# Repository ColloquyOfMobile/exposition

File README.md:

# exposition
Colloquy of Mobiles for exposition in ZKM

## Todo
In KiCad:
- Choose the footprint for power supply capacitor.
- Check dimension of jack barrel.
- For unexpected error on the Colloquy-PC, catch them, show them to the user, invite the user to add additional information, invite the user to log (with context), commit and push.

## Todo: software roadmap

Ordered by priority: get it running reliably first, then make it easy to
retune without code changes, then make faults easy to diagnose, then
polish the day-to-day experience.

### 1. Up and running (do this before anything else)

- **Validate on real hardware.** Everything built and tested this
  refactor ran in simulation (`Base.is_simulated` is only `False` on the
  `Colloquy-Laptop` hostname) - nothing has touched a real Dynamixel or
  Arduino yet. Run `main.py` on the actual machine and confirm servo
  comms, Arduino serial comms, and LED behavior before relying on
  anything else here.
- **Pin `requirements.txt` completely.** It only lists `yattag` and
  `dynamixel_sdk`, but `pyserial` (imported as `serial` in
  `hardware/arduino/`, `hardware/com_port/`, `hardware/u2d2/`) is a hard
  runtime dependency that isn't listed - `pip install -r
  requirements.txt` alone won't actually be enough to run the app on a
  fresh machine.
- **Implement `Colloquy.close()`.** Currently `raise
  NotImplementedError` unconditionally (with dead code after it) - there
  is no clean, non-emergency shutdown path besides the `/shutdown` web
  route. Decide what it should actually do (stop threads, release
  hardware) and implement it.
- **Decide the fate of the male-blink / female-read-pattern behavior.**
  This is the installation's actual interactive concept (see CLAUDE.md:
  each male blinks an identity + requested-drive-state pattern, a female
  is meant to read it and respond) - but `Search.loop()`/`setup()`
  deliberately `raise NotImplementedError("use the turn_back_and_forth
  thread")` right now, so females just turn back and forth instead. Is
  that simplification intentional/permanent for this exhibition, or does
  `ReadPattern` need to be wired up before opening? This is an artistic
  decision as much as a technical one - flag it and decide deliberately
  rather than by default.
- **Confirm the emergency-stop path is enough for unattended operation.**
  `/emergency-stop`, `/shutdown`, `/restart` exist and work, but this is
  a museum installation that will run unattended for stretches - is a
  web route sufficient, or is a physical panic button / auto-restart-on-
  crash needed too?
- **Test USB/serial resilience.** Arduino/U2D2 connections open lazily
  on first use; there's already a "waiting for Arduino to reboot"
  pattern at startup, but reconnect-after-fault (cable unplugged and
  replugged mid-show, Arduino resets on its own) hasn't been exercised.

### 2. Flexible (retune without touching code)

- The new **params tab** (`/app/params`) is the first big step here -
  every value in `local/params.json` is now live-viewable/editable from
  the web UI. Worth a pass during real setup to confirm the values staff
  will actually want to retune on-site (light thresholds, interaction
  origins, per-body drive timing) are all comfortably reachable there.
- **Decide what (if anything) in the `#`-prefixed archive is actually
  planned-but-unfinished work**, vs. permanently retired. CLAUDE.md
  preserves it as reference rather than dead code by convention, and this
  refactor found real orphaned/broken functionality nearby it (a
  `Conversation` concept, a `Mirror` concept, both deleted this pass as
  unreachable) - worth one deliberate pass to confirm nothing there was
  actually meant to ship.
- **Audit which hardcoded constants are likely to need on-site tuning**
  (e.g. the 0.5s blink step, the light-pattern bit sequences) and move
  the ones that do into `params.json` alongside everything else now that
  there's a UI for it.

### 3. Debuggable (diagnose faults quickly when something goes wrong)

- **Fix `ThreadErrors`/`ThreadError`'s stale one-arg `snapshot(path)`
  override** - it shadows the working inherited
  `Base.snapshot(path, focus_path)`, the same crash pattern fixed
  throughout this refactor everywhere else, but explicitly left for
  later since it only matters once a thread actually errors. That's
  exactly the moment you need it to work during a live show, so worth
  fixing before relying on it.
- **Build a live status/health view.** Right now, diagnosing anything
  means clicking through the generic tree browser node by node. A single
  page showing every body's position, torque state, and light-sensor
  reading, plus any `thread_errors`, at a glance would cut diagnosis time
  a lot during setup and rehearsal.
- **Put the chart tooling built this refactor to real use**
  (`ui/graph_view.py`, `tests > test graph`, `test_sensors`) - wire up
  light-sensor and position logging during rehearsal runs so behavior can
  be reviewed afterward, not only watched live.
- **Stop wiping logs on every restart.** `colloquy/logger.py` clears
  `local/logs/` on process start - if something crashes overnight
  unattended, the log explaining why is gone before anyone looks.
  Archive the previous run's logs instead of deleting them.
- **Coverage sits around 46%** on the new unit test suite - expected and
  fine, since hardware I/O and thread-loop bodies aren't unit-testable by
  design (confirmed this refactor, not a red flag by itself). It does
  mean bugs in `loop()`/`setup()`/`setdown()` bodies can only be caught
  by actually running them, so budget a deliberate rehearsal-testing pass
  on real hardware rather than trusting the test suite's green alone.

### 4. A bit more user-friendly (once the above is solid)

- The web UI is a generic tree browser - functional, but not really
  designed for a non-developer to operate confidently during a show.
  Once the above is stable, a small purpose-built front page (start/
  stop, current status, the handful of common actions) would go a long
  way for staff who don't know the underlying tree structure.
- Two small pre-existing bugs surfaced but left out of scope this
  refactor, worth a quick fix once things are stable: `input/__init__.py`'s
  `commands` property references undefined `Key`/`Space` (crashes if ever
  exercised); `hardware/neopixels/commands/close.py` and
  `tests/test_neopixels/commands/close.py` reference an undefined
  `HTML`/`Action` from an already-commented-out import.
- Once real rehearsal data exists (see "chart tooling" above), invest in
  presenting it well - the server-drawn graph already pages and thins, so
  this is mostly a matter of pointing it at real logged data.

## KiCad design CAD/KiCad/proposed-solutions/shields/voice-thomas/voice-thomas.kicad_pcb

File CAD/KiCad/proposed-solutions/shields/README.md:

# Colloquy shield PCB set

Updated for SHIELDS.md revision d076edc (2026-10-13) and MICROPHONE_BOARD.md.
All current KiCad 9 projects and their shared library are in this folder.

Blender assembly scenes, previews and export tools are in
[CAD/Blender/pcb-assemblies](../../../Blender/pcb-assemblies/README.md).

Matching functional pinouts show signal origins and destinations around a
rectangle, with processor pins in its centre:
[Arduino Mega](<../../../../Source code/Python/colloquy/server2/static/hardware/shields-mega-pinout.svg>)
and [Teensy](<../../../../Source code/Python/colloquy/server2/static/hardware/shields-teensy-pinout.svg>).
`SHIELDS.md` section 1a shows both. Regenerate from the repository root with
`py export_shields_pinout.py`; the generator checks its mapping against the PCBs.

| Project | Function | Quantity |
|---|---|---|
| backplane | Harness, power, shield slots, eight LEDs and 26 test headers | 1 |
| teensy-adapter | Teensy 4.1 in the Mega slot; three power test headers | 1 |
| voice-thomas | Thomas RC filter for either processor; THT pitch components | 5, more as needed |
| microphone-flex | Rev C MAX9814 holder, 32 x 62 mm, left/right/up module sockets, removable selectors | 6 (one spare) |
| analyser-carrier | Five converted DFRobot modules, direct plug-in sockets | 1 |

The active filter is obsolete. One voice layout supports all five Thomas
populations and thirteen new-pitch populations. See ASSEMBLY.md and its BOMs.
The old active voice and bare-chip analyser files are clearly archived under
../../old-reference/superseded-shields/ and are not current build inputs.

Open each current .kicad_pro. Main .kicad_pcb files are routed; -placed files
are unrouted checkpoints. Backplane/adapter use four copper layers; voice/mic
two; nominal thickness is 1.6 mm. Symbols and footprints are local.
Native ERC/DRC, netlist parity and interface results are in VALIDATION.md/json.

Current order packages are in ../../production/assembly/; see ../../README.md.
The analyser carrier uses user-authorized photo-derived mounts with tolerance slots; confirm fit with its 1:1 template. The microphone
module's actual pin/hole grid and seated connector height must be confirmed. REVIEW.md
lists outstanding physical checks. The carrier retains the original 150 x 55mm backplane envelope and retention points.

Generation: scripts/design.py, boards.py, variants.py with KiCad's Python.
The analyser carrier has its own generator, scripts/carrier.py; the microphone
holder is microphone-flex/microphone-flex.kicad_pcb; its README documents the
approved placement, routing and initial selector settings. The old holder generator
is historical and must not replace the selected flex board.
Routing: scripts/route.py with Freerouting 2.4.1. After routing, run labels.py,
finish.py, planes.py, check.py and verify.py, then the repository root's
mark_polarity.py (+ and - beside every polarized part). Preserve mechanical holes and
validated connector positions when regenerating. Historical migration scripts
are one-time tools, not general rebuild commands. Router files stay in tmp/.
positions.csv contains front SMD placements for outsourced boards; fit THT parts manually from BOMs
and assembly views. Filter all populations by their selected BOM.

All SMD parts are on the front. The adapter's CM1-CM5 are beside the Teensy
socket, clear of its body. Outsource front SMD assembly for the backplane,
adapter, voice card (R3) and flex microphone holder. Current manufacturing ZIPs
include exact SMD BOMs and matching CPL files. Fit through-hole parts and modules
by hand; the analyser carrier has no SMD population.

## Microphone on the module's L input — 2026-10-19

Each DFRobot module now takes its microphone on L, so the conversion moves to
the right channel: remove R3 (the right-input 22K) and jumper the isolated R
to OUT. The carrier schematic, routed copper, silkscreen and fabrication
packages now follow SHIELDS.md 4b and analyser-carrier/README.md
(RELEASE_REVIEW.md F7, resolved). All module and retention positions are preserved.

## Front computing slot and servo supply — 2026-10-08

The 2026-10-08 backplane also puts the computing slot on the DSUB/front face,
mirrored about x=167.83 mm, with holes matching the unchanged Teensy adapter.
USB/jack rule areas exclude pads and vias. Computing-slot spacers must be
round and <=4 mm OD on the front, with screw heads on the rear (ASSEMBLY.md).
+12V is routed at >=2 mm entirely on outer copper, enforced by native DRC
rules and independent verification.

## Direct-plug carrier revision — 2026-10-07

The analyser carrier now uses female sockets beneath modified modules. No
module-to-carrier leads remain. Each module requires removal of its left-input
22K resistor R4, an on-module jumper from isolated L to OUT, and downward
male headers (since 2026-10-19: R3 and R instead, above). Read
analyser-carrier/README.md before assembly. Socket positions
are photo-derived; check all contacts against the updated 1:1 template.

## Restored enclosure mounts — 2026-10-21

The backplane now retains the four original 8 mm enclosure cutouts recovered
from `CAD/KiCad/old-reference/original-supplied-boards/electronic box/`. Their centres are measured from the
outside board envelope, preserving the original pattern exactly. TPL3 moved
locally and affected tracks were rerouted to clear the centre and left holes.
See [the dimensions and transfer notes](<backplane/ENCLOSURE_MOUNTING.md>) and
[the mounting layout](<backplane/enclosure-mounting-layout.svg>).
After regenerating a staging board, run `scripts/restore_enclosure_holes.py`
before routing; rerun DRC and export fabrication files after any layout edit.

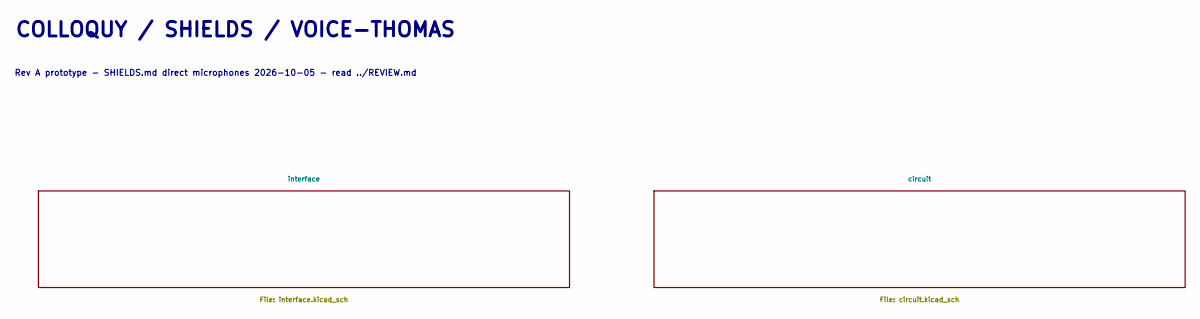
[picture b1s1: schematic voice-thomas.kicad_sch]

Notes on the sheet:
COLLOQUY / SHIELDS / VOICE-THOMAS
Rev A prototype - SHIELDS.md direct microphones 2026-10-05 - read ../REVIEW.md

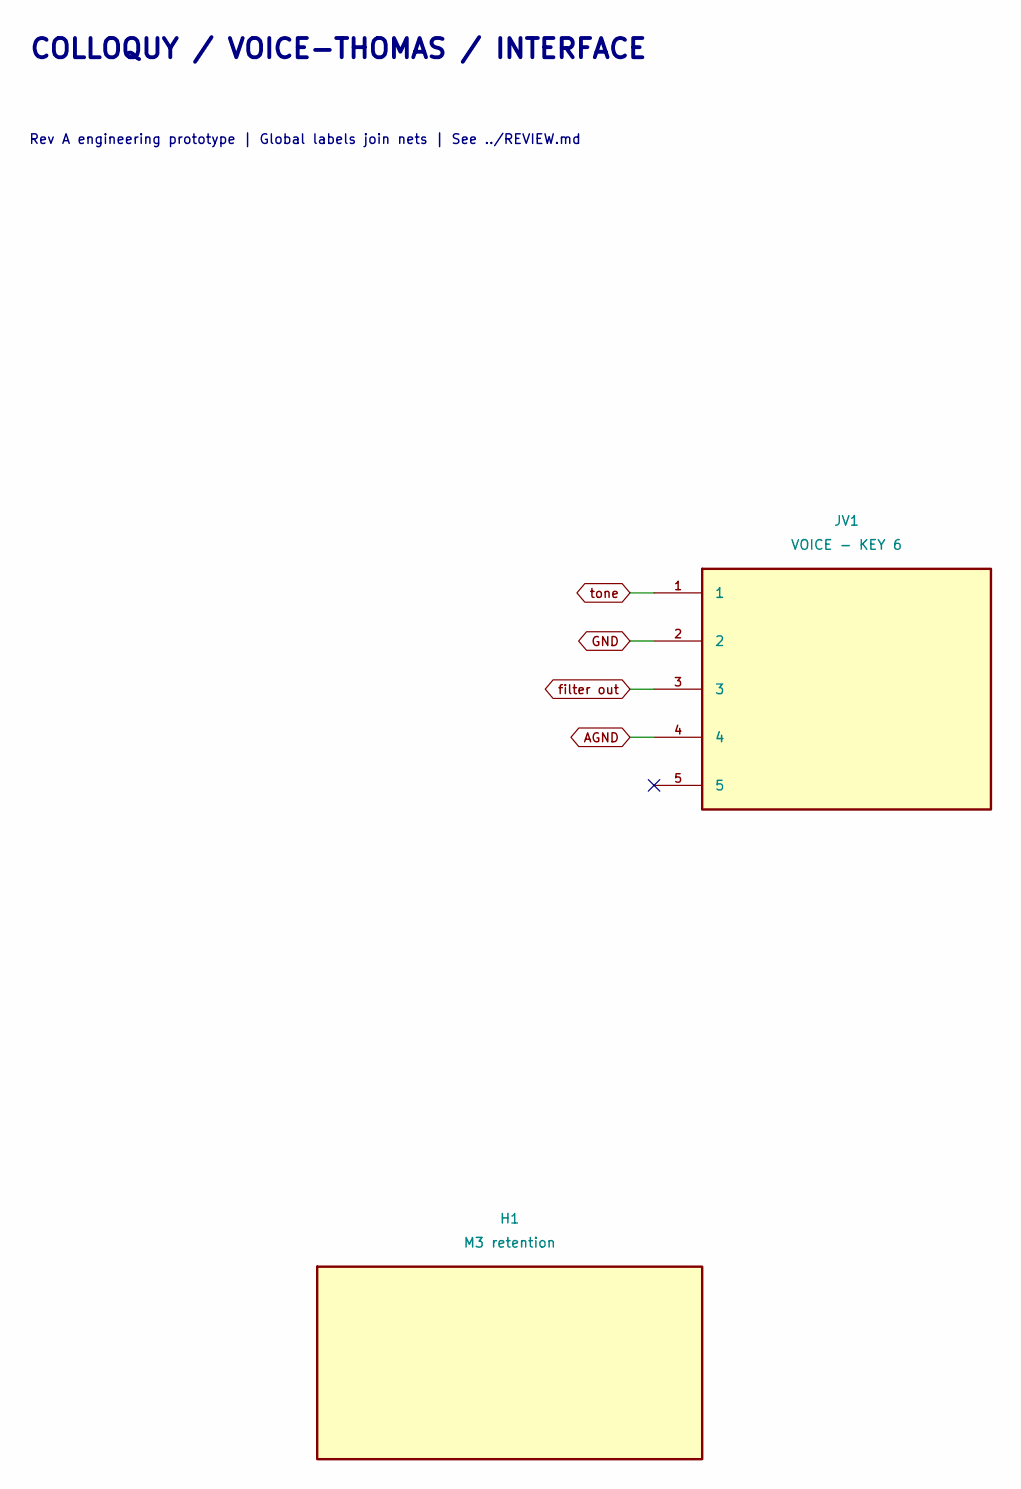
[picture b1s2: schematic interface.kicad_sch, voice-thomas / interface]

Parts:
H1: M3 retention; MountingHole_3.2mm_M3
JV1: VOICE - KEY 6; Socket_2x03_Key6

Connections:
AGND: JV1.4; also elsewhere on the board
GND: JV1.2; also elsewhere on the board
filter out: JV1.3; also elsewhere on the board
tone: JV1.1; also elsewhere on the board

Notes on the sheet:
COLLOQUY / VOICE-THOMAS / INTERFACE
Rev A engineering prototype | Global labels join nets | See ../REVIEW.md

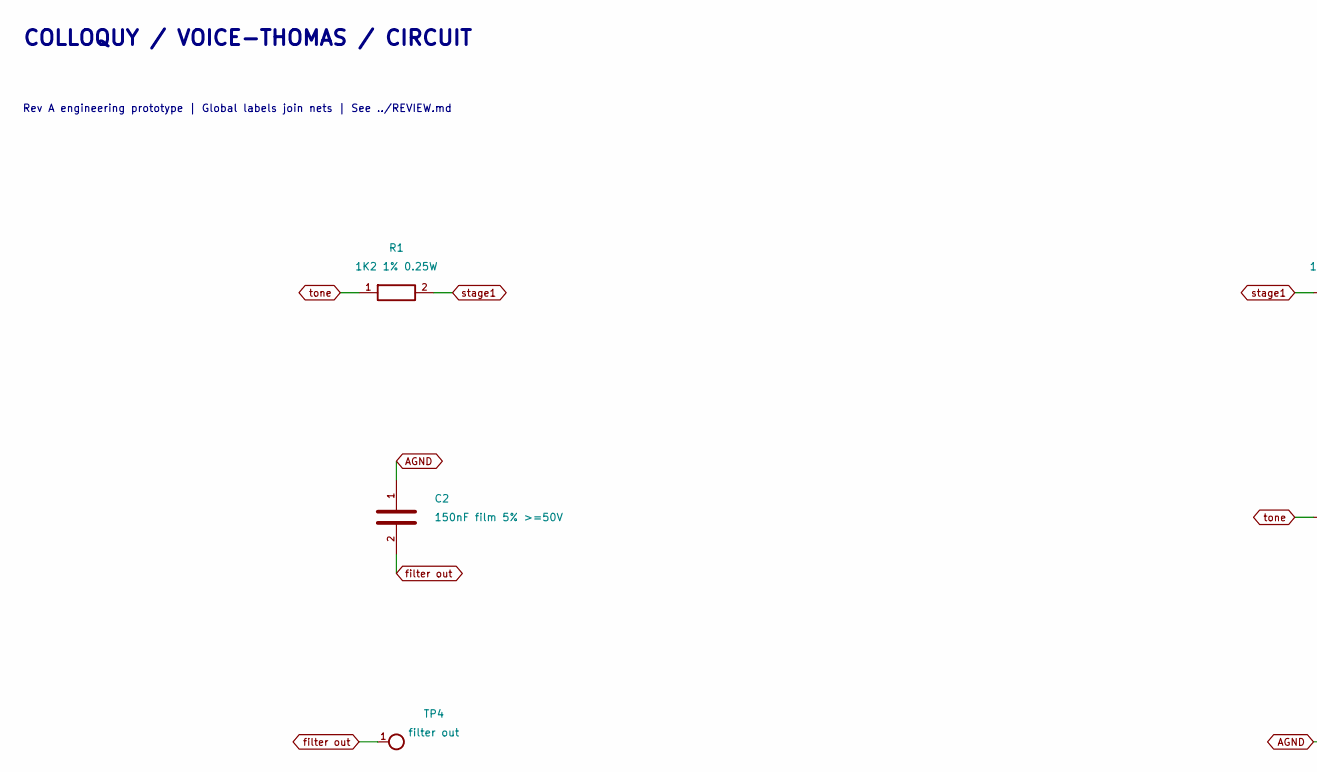
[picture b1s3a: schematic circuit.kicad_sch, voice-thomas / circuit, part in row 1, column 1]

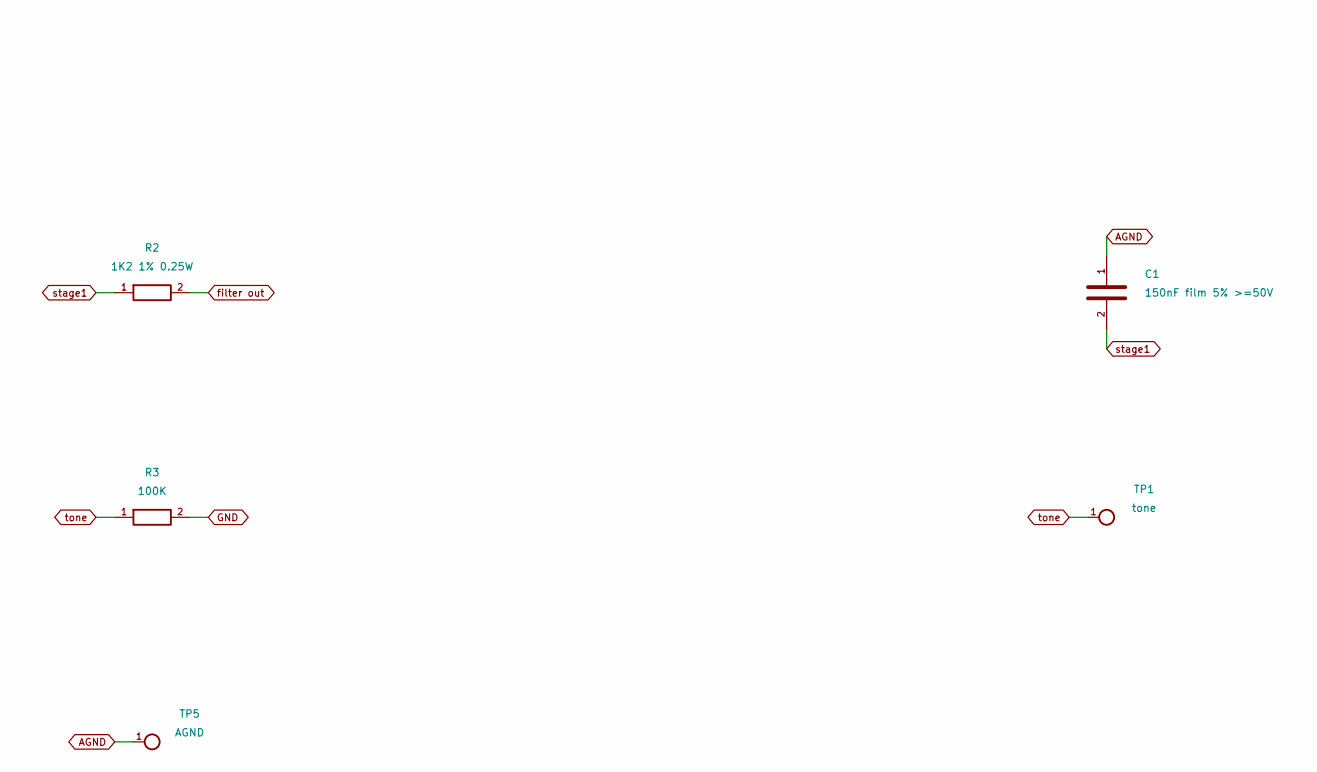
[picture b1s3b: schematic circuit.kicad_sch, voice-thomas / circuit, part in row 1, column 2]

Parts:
C1, C2: 150nF film 5% >=50V; C_Rect_L7.0mm_W6.5mm_P5.00mm
R1, R2: 1K2 1% 0.25W; R_Axial_DIN0207_L6.3mm_D2.5mm_P7.62mm_Horizontal
R3: 100K; R_Axial_DIN0207_L6.3mm_D2.5mm_P7.62mm_Horizontal
TP1: tone; TestPoint_Pad_D1.5mm
TP4: filter out; TestPin_1x01_P2.54mm
TP5: AGND; TestPin_1x01_P2.54mm

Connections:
AGND: C1.1, C2.1, TP5.1; also elsewhere on the board
GND: R3.2; also elsewhere on the board
filter out: C2.2, R2.2, TP4.1; also elsewhere on the board
stage1: C1.2, R1.2, R2.1
tone: R1.1, R3.1, TP1.1; also elsewhere on the board

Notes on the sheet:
COLLOQUY / VOICE-THOMAS / CIRCUIT
Rev A engineering prototype | Global labels join nets | See ../REVIEW.md

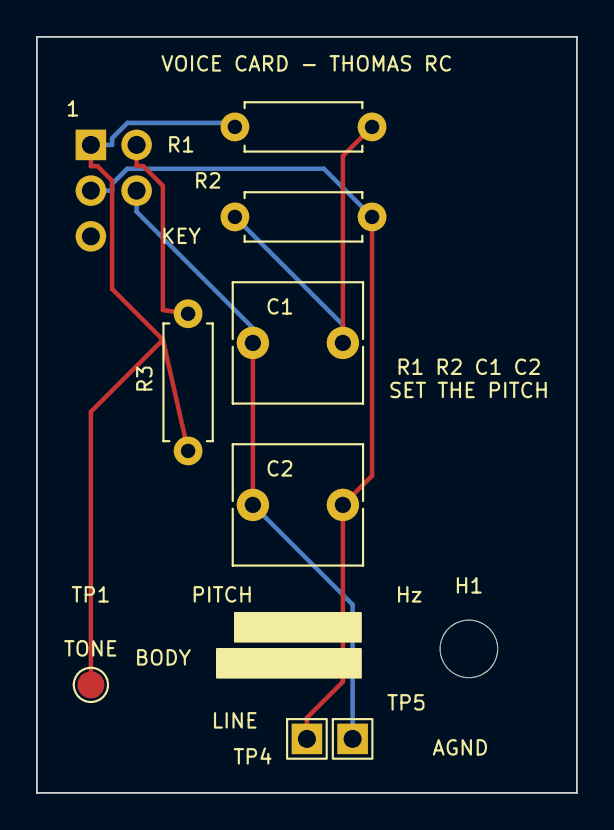
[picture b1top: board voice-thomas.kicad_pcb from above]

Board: 2 copper layers, 30.0 x 42.0 mm, 10 parts (1 on the bottom side), 5 nets.

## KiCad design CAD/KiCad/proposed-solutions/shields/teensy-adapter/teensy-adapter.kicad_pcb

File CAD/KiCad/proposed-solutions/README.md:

# Editable designs

Current replacement designs and alternatives live here. Only the seven boards listed
in [the electronics index](../README.md) are selected for manufacture. In particular,
`electronic box v2` and `thomas-or-teensy` are alternative main-board studies.

Use `shields/microphone-flex` for the production microphone holder. Original boards
are preserved under `../old-reference`; purchased-module references are under
`../provided-elements`. Generated order files are under `../production`.

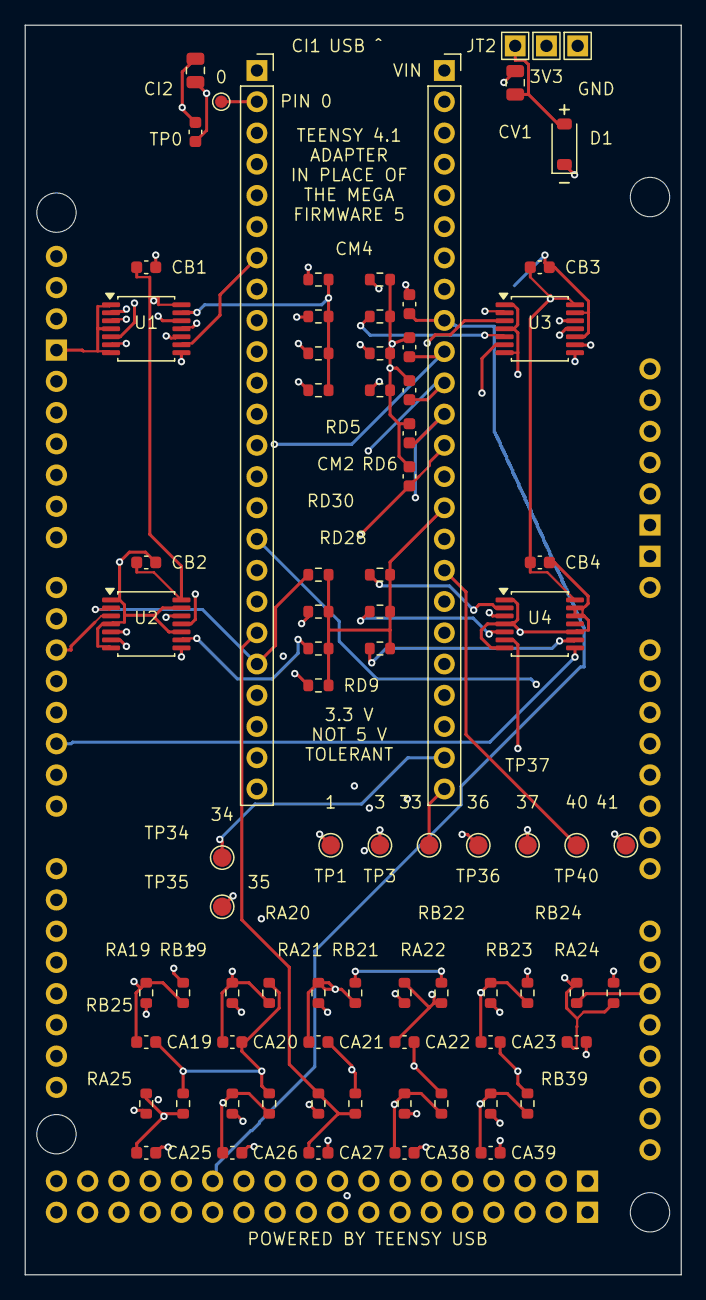
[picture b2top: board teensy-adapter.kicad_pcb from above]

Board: 4 copper layers, 53.3 x 101.6 mm, 85 parts (1 on the bottom side), 71 nets.

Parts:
CA19, CA20, CA21, CA22, CA23, CA24, CA25, CA26, CA27, CA38, CA39: 10nF C0G; C_0603_1608Metric
CB1, CB2, CB3, CB4: 100nF; C_0603_1608Metric
CI1: 10uF X7R; C_0805_2012Metric
CI2: 100nF; C_0603_1608Metric
CM1, CM2, CM3, CM4, CM5: 1nF C0G; C_0603_1608Metric
CV1: 10uF X7R; C_0805_2012Metric
D1: 1N5819HW; D_SOD-123
HM1, HM2, HM3, HM4: M3 computing shield; MountingHole_3.2mm_M3
JM1: MEGA PATTERN FEMALE; Mega_Female
JT1: Teensy 4.1 JT1; PinSocket_1x24_P2.54mm_Vertical
JT2: Teensy 4.1 JT2; PinSocket_1x24_P2.54mm_Vertical
RA19, RA20, RA21, RA22, RA23, RA24, RA25, RA26, RA27, RA38, RA39: 100K; R_0603_1608Metric
RB19, RB20, RB21, RB22, RB23, RB24, RB25, RB26, RB27, RB38, RB39: 150K; R_0603_1608Metric
RD2, RD4, RD5, RD6, RD7, RD8, RD9, RD10, RD11, RD12, RD28, RD29, RD30, RD31, RD32: 100K; R_0603_1608Metric
TP0: gpio/0; TestPoint_Pad_D1.0mm
TP1: gpio/1; TestPoint_Pad_D1.5mm
TP3: gpio/3; TestPoint_Pad_D1.5mm
TP33: gpio/33; TestPoint_Pad_D1.5mm
TP34: gpio/34; TestPoint_Pad_D1.5mm
TP35: gpio/35; TestPoint_Pad_D1.5mm
TP36: gpio/36; TestPoint_Pad_D1.5mm
TP37: gpio/37; TestPoint_Pad_D1.5mm
TP40: gpio/40; TestPoint_Pad_D1.5mm
TP41: gpio/41; TestPoint_Pad_D1.5mm
TPG: GND; TestPin_1x01_P2.54mm
TPI: IOREF; TestPin_1x01_P2.54mm
TPV: VIN_USB; TestPin_1x01_P2.54mm
U1, U2, U3, U4: SN74LV4T125PWR; TSSOP-14_4.4x5mm_P0.65mm

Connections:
GND: CA19.2, CA20.2, CA21.2, CA22.2, CA23.2, CA24.2, CA25.2, CA26.2, CA27.2, CA38.2, CA39.2, CB1.2, CB2.2, CB3.2, CB4.2, CI1.2, CI2.2, CM1.2, CM2.2, CM3.2, CM4.2, CM5.2, CV1.2, JM1.GND1, JM1.GND2, JM1.GND3, JM1.GND5, JM1.GND6, JT1.1, JT2.2, JT2.15, RB19.2, RB20.2, RB21.2, RB22.2, RB23.2, RB24.2, RB25.2, RB26.2, RB27.2, RB38.2, RB39.2, RD2.2, RD4.2, RD5.2, RD6.2, RD7.2, RD8.2, RD9.2, RD10.2, RD11.2, RD12.2, RD28.2, RD29.2, RD30.2, RD31.2, RD32.2, TPG.1, U1.1, U1.4, U1.7, U1.10, U1.13, U2.1, U2.4, U2.7, U2.10, U2.13, U3.1, U3.4, U3.7, U3.10, U3.13, U4.1, U4.4, U4.7, U4.10, U4.12, U4.13
IOREF: CI1.1, CI2.1, JT1.15, JT2.3, TPI.1
MEGA_5V: D1.1, JM1.5V1, JM1.5V3, JM1.5V4
VIN_USB: CB1.1, CB2.1, CB3.1, CB4.1, CV1.1, D1.2, JT2.1, TPV.1, U1.14, U2.14, U3.14, U4.14
adc/19: CA19.1, JT2.8, RA19.2, RB19.1
adc/20: CA20.1, JT2.7, RA20.2, RB20.1
adc/21: CA21.1, JT2.6, RA21.2, RB21.1
adc/22: CA22.1, JT2.5, RA22.2, RB22.1
adc/23: CA23.1, JT2.4, RA23.2, RB23.1
adc/24: CA24.1, JT1.16, RA24.2, RB24.1
adc/25: CA25.1, JT1.17, RA25.2, RB25.1
adc/26: CA26.1, JT1.18, RA26.2, RB26.1
adc/27: CA27.1, JT1.19, RA27.2, RB27.1
adc/38: CA38.1, JT2.19, RA38.2, RB38.1
adc/39: CA39.1, JT2.18, RA39.2, RB39.1
amp shutdown: JM1.D2, U4.8
female1/mic direct: CM1.1, JM1.D26, JT2.13
female1/neopixel/driven: JM1.D14, U2.6
female1/photosensor: JM1.A5, RA19.1
female1/tone: JM1.D6, U1.3
female2/mic direct: CM2.1, JM1.D27, JT2.12
female2/neopixel/driven: JM1.D7, U2.8
female2/photosensor: JM1.A6, RA20.1
female2/tone: JM1.D46, U1.6
female3/mic direct: CM3.1, JM1.D28, JT2.11
female3/neopixel/driven: JM1.D8, U2.11
female3/photosensor: JM1.A7, RA21.1
female3/tone: JM1.D10, U1.8
gpio/0: JT1.2, TP0.1
gpio/1: JT1.3, TP1.1
gpio/2: JT1.4, RD2.1, U1.2
gpio/3: JT1.5, TP3.1
gpio/4: JT1.6, RD4.1, U1.5
gpio/5: JT1.7, RD5.1, U1.9
gpio/6: JT1.8, RD6.1, U1.12
gpio/7: JT1.9, RD7.1, U2.5
gpio/8: JT1.10, RD8.1, U2.9
gpio/9: JT1.11, RD9.1, U2.12
gpio/10: JT1.12, RD10.1, U3.2
gpio/11: JT1.13, RD11.1, U3.5
gpio/12: JT1.14, RD12.1, U3.9
gpio/28: JT1.20, RD28.1, U2.2
gpio/29: JT1.21, RD29.1, U3.12
gpio/30: JT1.22, RD30.1, U4.2
gpio/31: JT1.23, RD31.1, U4.5
gpio/32: JT1.24, RD32.1, U4.9
gpio/33: JT2.24, TP33.1
gpio/34: JT2.23, TP34.1
gpio/35: JT2.22, TP35.1
gpio/36: JT2.21, TP36.1
gpio/37: JT2.20, TP37.1
gpio/40: JT2.17, TP40.1
gpio/41: JT2.16, TP41.1
male1/aux driven: JM1.D24, U4.3
male1/bar neopixel/driven: JM1.D16, U3.11
male1/mic direct: CM4.1, JM1.D29, JT2.10
male1/neopixel/driven: JM1.D9, U3.3
male1/photosensor/A: JM1.A8, RA22.1
male1/photosensor/B: JM1.A9, RA23.1
male1/photosensor/C: JM1.A10, RA24.1
male1/photosensor/D: JM1.A11, RA25.1
male1/tone: JM1.D11, U1.11
male2/aux driven: JM1.D25, U4.6
male2/bar neopixel/driven: JM1.D17, U3.8
male2/mic direct: CM5.1, JM1.D30, JT2.9
male2/neopixel/driven: JM1.D15, U3.6
male2/photosensor/A: JM1.A12, RA26.1
male2/photosensor/B: JM1.A13, RA27.1
male2/photosensor/C: JM1.A14, RA38.1
male2/photosensor/D: JM1.A15, RA39.1
male2/tone: JM1.D5, U2.3

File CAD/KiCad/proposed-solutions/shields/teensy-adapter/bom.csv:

Reference,Value,Footprint,MPN,Assembly
JM1,MEGA PATTERN FEMALE,Shields:Mega_Female,,fit
CM1,1nF C0G,Shields:C_0603_1608Metric,,fit
CM2,1nF C0G,Shields:C_0603_1608Metric,,fit
CM3,1nF C0G,Shields:C_0603_1608Metric,,fit
CM4,1nF C0G,Shields:C_0603_1608Metric,,fit
CM5,1nF C0G,Shields:C_0603_1608Metric,,fit
JT1,Teensy 4.1 JT1,Shields:PinSocket_1x24_P2.54mm_Vertical,,fit
JT2,Teensy 4.1 JT2,Shields:PinSocket_1x24_P2.54mm_Vertical,,fit
RD2,100K,Shields:R_0603_1608Metric,,fit
RD4,100K,Shields:R_0603_1608Metric,,fit
RD5,100K,Shields:R_0603_1608Metric,,fit
RD6,100K,Shields:R_0603_1608Metric,,fit
U1,SN74LV4T125PWR,Shields:TSSOP-14_4.4x5mm_P0.65mm,SN74LV4T125PWR,fit
CB1,100nF,Shields:C_0603_1608Metric,,fit
RD28,100K,Shields:R_0603_1608Metric,,fit
RD7,100K,Shields:R_0603_1608Metric,,fit
RD8,100K,Shields:R_0603_1608Metric,,fit
RD9,100K,Shields:R_0603_1608Metric,,fit
U2,SN74LV4T125PWR,Shields:TSSOP-14_4.4x5mm_P0.65mm,SN74LV4T125PWR,fit
CB2,100nF,Shields:C_0603_1608Metric,,fit
RD10,100K,Shields:R_0603_1608Metric,,fit
RD11,100K,Shields:R_0603_1608Metric,,fit
RD12,100K,Shields:R_0603_1608Metric,,fit
RD29,100K,Shields:R_0603_1608Metric,,fit
U3,SN74LV4T125PWR,Shields:TSSOP-14_4.4x5mm_P0.65mm,SN74LV4T125PWR,fit
CB3,100nF,Shields:C_0603_1608Metric,,fit
RD30,100K,Shields:R_0603_1608Metric,,fit
RD31,100K,Shields:R_0603_1608Metric,,fit
RD32,100K,Shields:R_0603_1608Metric,,fit
U4,SN74LV4T125PWR,Shields:TSSOP-14_4.4x5mm_P0.65mm,SN74LV4T125PWR,fit
CB4,100nF,Shields:C_0603_1608Metric,,fit
RA19,100K,Shields:R_0603_1608Metric,,fit
RB19,150K,Shields:R_0603_1608Metric,,fit
CA19,10nF C0G,Shields:C_0603_1608Metric,,fit
RA20,100K,Shields:R_0603_1608Metric,,fit
RB20,150K,Shields:R_0603_1608Metric,,fit
CA20,10nF C0G,Shields:C_0603_1608Metric,,fit
RA21,100K,Shields:R_0603_1608Metric,,fit
RB21,150K,Shields:R_0603_1608Metric,,fit
CA21,10nF C0G,Shields:C_0603_1608Metric,,fit
RA22,100K,Shields:R_0603_1608Metric,,fit
RB22,150K,Shields:R_0603_1608Metric,,fit
CA22,10nF C0G,Shields:C_0603_1608Metric,,fit
RA23,100K,Shields:R_0603_1608Metric,,fit
RB23,150K,Shields:R_0603_1608Metric,,fit
CA23,10nF C0G,Shields:C_0603_1608Metric,,fit
RA24,100K,Shields:R_0603_1608Metric,,fit
RB24,150K,Shields:R_0603_1608Metric,,fit
CA24,10nF C0G,Shields:C_0603_1608Metric,,fit
RA25,100K,Shields:R_0603_1608Metric,,fit
RB25,150K,Shields:R_0603_1608Metric,,fit
CA25,10nF C0G,Shields:C_0603_1608Metric,,fit
RA26,100K,Shields:R_0603_1608Metric,,fit
RB26,150K,Shields:R_0603_1608Metric,,fit
CA26,10nF C0G,Shields:C_0603_1608Metric,,fit
RA27,100K,Shields:R_0603_1608Metric,,fit
RB27,150K,Shields:R_0603_1608Metric,,fit
CA27,10nF C0G,Shields:C_0603_1608Metric,,fit
RA38,100K,Shields:R_0603_1608Metric,,fit
RB38,150K,Shields:R_0603_1608Metric,,fit
CA38,10nF C0G,Shields:C_0603_1608Metric,,fit
RA39,100K,Shields:R_0603_1608Metric,,fit
RB39,150K,Shields:R_0603_1608Metric,,fit
CA39,10nF C0G,Shields:C_0603_1608Metric,,fit
D1,1N5819HW,Shields:D_SOD-123,1N5819HW,fit
CV1,10uF X7R,Shields:C_0805_2012Metric,,fit
CI1,10uF X7R,Shields:C_0805_2012Metric,,fit
CI2,100nF,Shields:C_0603_1608Metric,,fit
TPV,VIN_USB,Shields:TestPin_1x01_P2.54mm,,fit
TPI,IOREF,Shields:TestPin_1x01_P2.54mm,,fit
TPG,GND,Shields:TestPin_1x01_P2.54mm,,fit

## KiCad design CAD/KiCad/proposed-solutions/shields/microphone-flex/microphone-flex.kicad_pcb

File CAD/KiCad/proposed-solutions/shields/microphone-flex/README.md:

# Microphone holder Rev C — left, right or upward

## Side modules hang down — 2026-10-20

J2 and J3 modules are turned 180 degrees about the horizontal socket insertion
axis, so their bodies hang below the carrier PCB. M1 remains upward.
The socket footprints and all other component positions are unchanged.
This turn reverses the module's five-pin order along each side socket;
J2/J3 are rewired and the carrier is rerouted to match. Do not use the earlier
side-socket pin mapping with this orientation.

## User-approved placement — 2026-10-20

The routed board follows the saved microphone-flex-placed layout exactly:
all 16 footprint positions, rotations and sides are retained. Routing uses
the placement project's nominal 0.20 mm track width and clearance, with
router pad neckdowns subject to the project's minimum-width rules. J2/J3
overhang the PCB; their off-board outlines are on F.Fab rather than printed
silkscreen. The left/right footprint variants preserve the same pads and bodies.

Only H1/H2 frame slots remain. H3-H8 module-support mounting holes were removed
in the user's placement and are absent from the current schematic and views.
The older support STL/STEP files are retained as reference geometry; they are
not installed in the current variants. Side module views follow the moved
socket rows. Module retention requires a separate mechanical arrangement.

## Removable selectors — 2026-10-20

JP1 and JP2 are gold plated 1x03, 2.54 mm through-hole headers, each supplied
with one removable two-contact shunt. They replace the fixed R1/R2 zero-ohm
links on the current microphone flex board. The older Rev B microphone board
is retained as a historical design and is preserved under `../../../old-reference/microphone-rev-b/`.

Both headers have pad 1 = GND and pad 3 = filtered VDD. Pad 2 is GAIN on JP1
and A/R on JP2. Install exactly one shunt per selector, or leave it off for
the open setting:

| Selector | Shunt 1–2 | Shunt 2–3 | No shunt | Initial assembly |
| --- | --- | --- | --- | --- |
| JP1 maximum gain | 50 dB | 40 dB | 60 dB | 2–3: 40 dB |
| JP2 attack/release | 1:500 | 1:2000 | 1:4000 | 1–2: 1:500 |

The gain figures apply before automatic gain compression. Switch power off
before moving shunts. The centre signal pins feed all three alternative
module sockets; only one MAX9814 module is fitted. The initial settings
preserve the former electrical configuration while allowing later adjustment.
The schematic shows the three separate selector contacts; the removable
shunt positions are assembly instructions, not permanent PCB copper bridges.
The 3D files show generic shunt proxies at the initial positions. Purchased
header/shunt dimensions, access beneath the module, and physical fit still
need checking.

## Continuous-wire schematic for review

Open wired/microphone-flex-wired.kicad_pro for the separate editable reading
copy, or wired/microphone-flex-wired.pdf for the single A3 sheet. The SVG and
PNG preview are alongside it. Every connection is drawn with continuous wires;
the signal captions are plain text, not electrical labels. Dots mark joined
wires; crossings without dots are separate.

The three socket symbols align pins by signal for easier tracing. Their
physical pad numbers are retained, including the downward J2/J3 mapping.
J1 also groups its pins by signal rather than physical order. Fit one module
only. Component references, values, footprints, mounting holes, and electrical
connections follow the current source schematic and PCB.

Regenerate and validate from the repository root:

~~~powershell
& 'C:/Program Files/KiCad/9.0/bin/python.exe' CAD/KiCad/proposed-solutions/shields/microphone-flex/build_wired_schematic.py
& 'C:/Program Files/KiCad/9.0/bin/python.exe' CAD/KiCad/proposed-solutions/shields/microphone-flex/verify_wired_schematic.py
& 'C:/Program Files/KiCad/9.0/bin/kicad-cli.exe' sch export pdf -o CAD/KiCad/proposed-solutions/shields/microphone-flex/wired/microphone-flex-wired.pdf CAD/KiCad/proposed-solutions/shields/microphone-flex/wired/microphone-flex-wired.kicad_sch
& 'C:/Program Files/KiCad/9.0/bin/kicad-cli.exe' sch export svg -o CAD/KiCad/proposed-solutions/shields/microphone-flex/wired/ CAD/KiCad/proposed-solutions/shields/microphone-flex/wired/microphone-flex-wired.kicad_sch
pdftoppm -scale-to 2600 -png -singlefile CAD/KiCad/proposed-solutions/shields/microphone-flex/wired/microphone-flex-wired.pdf CAD/KiCad/proposed-solutions/shields/microphone-flex/wired/preview
~~~

The wired/validation.json report records 38 connected pins across eight nets,
agreement with the independently exported original schematic, circuit manifest
and PCB, zero electrical labels, and zero ERC violations. The wired copy
changes the presentation; these checks do not establish physical hardware
performance.

Prototype based on the user's annotated picture, 2026-10-15. The support PCB
stays on the aluminium profile; **one MAX9814 module** faces left, right or up.
This Rev C flex holder is selected for production. The historical Rev B board
and its existing fabrication package remain unchanged.

The PCB is **32 × 62 mm**, widened from 20 mm while retaining the 62 mm length
and 50 mm frame-fixing spacing. Its two **12 × 5.5 mm NPTH oblong slots** run
across the profile, with 6.5 mm between the semicircular end centres. The
18.5 × 12 mm capsule-shaped copper/part keepouts cover the entire slot travel,
not just the middle of each hole. The nominal 5 mm insulating frame spacers
remain separate from the module supports. Check washers, screw engagement and
the actual imperial profile/T-nuts before selecting frame fixings.

## Choose one module position

| Position | Socket | Module support |
| --- | --- | --- |
| Up / position 3 | M1, vertical 1×5 socket | Separate retention; no PCB support holes |
| Left / down / position 1 | J2, horizontal 1×5 socket | Separate retention; no PCB support holes |
| Right / down / position 2 | J3, opposing horizontal 1×5 socket | Separate retention; no PCB support holes |

All three socket rows carry the same five signals. **Fit exactly one module.**
The gain and A/R settings use the removable selectors above. The supply filter,
output resistor, LED and external J1 pin order are retained from Rev B.
J1 remains GND / +5V / OUT. SMD parts remain
on the front. Socket rows may all be populated, but fit only one module.
Do not force a module into a socket of unverified geometry.

With the side modules hanging down, all three sockets have the same physical
pad-to-signal mapping:

| Physical socket pad | M1 up | J2 left / J3 right |
| --- | --- | --- |
| 1 | GND | GND |
| 2 | Vdd | Vdd |
| 3 | Gain | Gain |
| 4 | Out | Out |
| 5 | AR | AR |

This follows the rotations of the original module, rather than assuming
pin-1-to-pin-1 geometry for a right-angle socket. Independent checks compare
all ten side contacts against the original module pad coordinates and nets.
Generic KiCad socket proxies set the nominal contact axis at 1.27 mm above
the holder component face. The side module underside is 2.54 mm outside the
socket mouth; the existing 6 mm pin projection gives 3.46 mm nominal insertion.
Purchased sockets, header seating and the actual violet module must be measured.

The downward side module extends nominally 22.733 mm below the carrier's
component face (21.133 mm below its underside). The CAD model clears the
solid carrier envelope; physical installation and frame clearance still
require checking. The earlier reference study used two
insulating arms at its M2 mounting holes, 10.033 mm apart. These arms are
not installed in the current user placement.
The four arm STL files in `3dmodels/` are **fitting prototypes**, with 2.2 mm
holes for insulating M2 fixings. Module screw heads must remain no larger than
4 mm beside the microphone capsule. Frame screws, module screws and cable
routes are not represented as verified purchased hardware. Print and dry-fit
the arms before relying on their dimensions or mechanical stiffness.

## Files and 3D views

`microphone-flex.kicad_pro` opens the selected routed production design. Its board
contains the three socket footprints and the two frame slots.
`variants/up.kicad_pcb`, `left.kicad_pcb` and `right.kicad_pcb` are assembled
viewing copies with identical copper and exactly one seated module. Their
3D references resolve to local repository models. The shared combined Blender
file in `../../../../Blender/pcb-assemblies/` is self-contained and adds six body scenes:

- Female body / Male body: upward module.
- Female body - mic left / Male body - mic left.
- Female body - mic right / Male body - mic right.

Earlier edited body scenes are retained as **Rev B reference** scenes.
The Mega and Teensy rack scenes are retained. The aluminium profile is still
the explicitly unconfirmed 1 × 2 inch reference described in the assembly
README; no installed TJ part number was found.

## Generation and verification

Run from the repository root:

```powershell
& 'C:/Program Files/KiCad/9.0/bin/python.exe' CAD/KiCad/proposed-solutions/shields/scripts/microphone_flex.py
& 'C:/Program Files/FreeCAD 1.0/bin/python.exe' CAD/KiCad/proposed-solutions/shields/microphone-flex/build_down_modules.py
& 'C:/Program Files/KiCad/9.0/bin/python.exe' CAD/KiCad/proposed-solutions/shields/scripts/route.py --only microphone-flex --preserve-netclasses --jar tmp/shields-tools/freerouting-2.4.1.jar --work tmp/microphone-flex-route
& 'C:/Program Files/KiCad/9.0/bin/python.exe' CAD/KiCad/proposed-solutions/shields/microphone-flex/check_layout.py
& 'C:/Program Files/KiCad/9.0/bin/python.exe' CAD/KiCad/proposed-solutions/shields/microphone-flex/export_variants.py
& 'C:/Program Files/Blender Foundation/Blender 5.2/blender.exe' --background --python-exit-code 1 --python CAD/Blender/pcb-assemblies/scripts/update_visual_geometry.py -- --only=shield-configurations.blend --render
```

For a newly edited placement, rebuild the downward models before routing; the first command
recreates the staging board from the generator's recorded placement. The final
command refreshes meshes in place while retaining scene edits and placements.

`layout-validation.json`: zero ERC/DRC violations and zero unconnected items;
all 38 connected pins agree between the native schematic, circuit manifest
and PCB. Slot geometry and spacing, side pin polarity, and contact alignment
are independently checked. `support-model-validation.json` describes only the
older reference support solids, not the current mounting arrangement. The
side-down-validation.json report verifies the current module transforms,
negative Z extent and absence of intersection with the carrier envelope. `variant-validation.json` and
the assembly's `body-scenes-validation.json` record source/output hashes.
Simulation and CAD checks do not establish physical fit, acoustic performance,
vibration isolation or mechanical strength. No fabrication release is claimed.

Sources and attribution: Rev B microphone holder; retained Adafruit MAX9814
reference (Limor Fried/Ladyada, CC BY-SA 3.0; see
`../max9814-reference/source/license.txt`); generic KiCad connector geometry
(CC BY-SA 4.0 with library exception). New support arms are provisional geometry
for this installation.

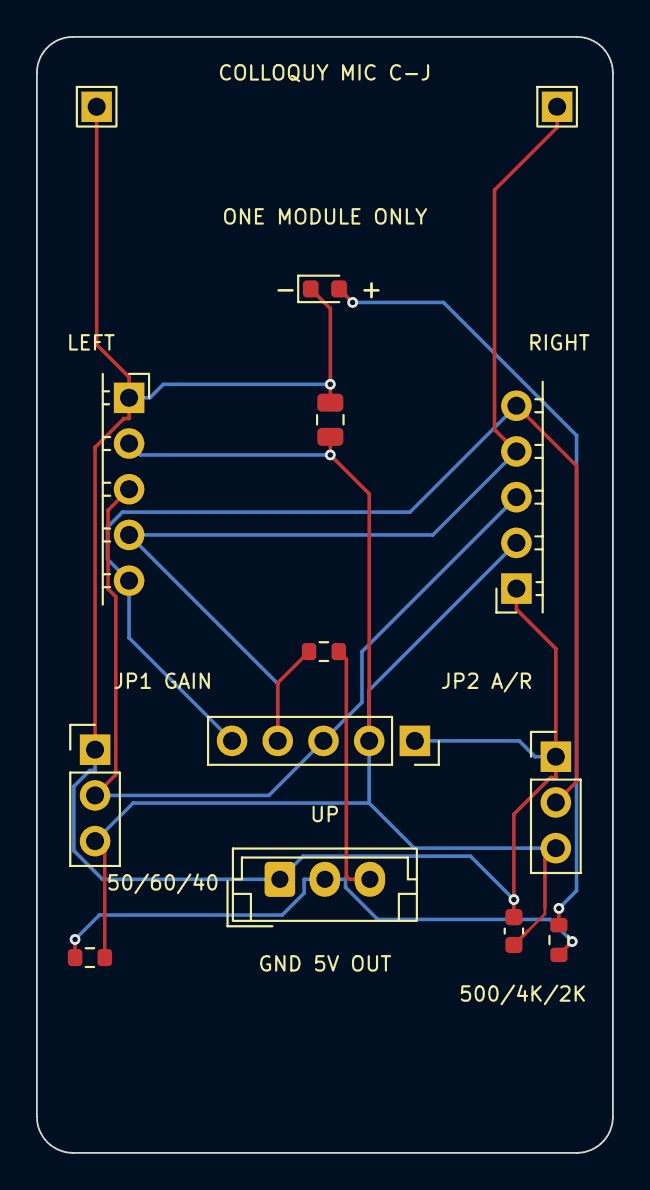
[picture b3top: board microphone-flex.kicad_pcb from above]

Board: 2 copper layers, 32.0 x 62.0 mm, 16 parts (0 on the bottom side), 8 nets.

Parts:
C6: 100nF; C_0603_1608Metric
C7: 22uF X5R 10V; C_0805_2012Metric
D1: GREEN LED; LED_0603_1608Metric
H1, H2: M5 SLOT 12x5.5 / TRANSVERSE; Flex_M5_Slot12x5.5_Keepout
J1: GND / +5V / OUT; JST_EH_B3B-EH-A_1x03_P2.50mm_Vertical
J2: LEFT / DOWNWARD MODULE; Flex_Socket_Left_Overhang
J3: RIGHT / DOWNWARD MODULE; Flex_Socket_Right_Overhang
JP1: GAIN SELECT / HEADER + SHUNT; Flex_Gain_Selector
JP2: AR SELECT / HEADER + SHUNT; Flex_AR_Selector
M1: UP / ONE MODULE ONLY; Flex_Socket_Up
R4: 33R; R_0603_1608Metric
R5: 470R; R_0603_1608Metric
R6: 2K2; R_0603_1608Metric
TP1: MICOUT; TestPin_1x01_P2.54mm
TP2: GND; TestPin_1x01_P2.54mm

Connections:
+5V: J1.2, R4.1, R6.1
AR: J2.5, J3.5, JP2.2, M1.5
GAIN: J2.3, J3.3, JP1.2, M1.3
GND: C6.2, C7.2, D1.1, J1.1, J2.1, J3.1, JP1.1, JP2.1, M1.1, TP2.1
MICOUT: J2.4, J3.4, M1.4, R5.1, TP1.1
OUT: J1.3, R5.2
VDD: C6.1, C7.1, J2.2, J3.2, JP1.3, JP2.3, M1.2, R4.2
led/D1: D1.2, R6.2

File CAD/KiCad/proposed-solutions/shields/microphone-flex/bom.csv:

Reference,Value,Footprint,MPN,Assembly
M1,UP / ONE MODULE ONLY,Shields:Flex_Socket_Up,Existing MAX9814 module + 1x05 2.54mm female socket,fit
R4,33R,Shields:R_0603_1608Metric,,fit
C7,22uF X5R 10V,Shields:C_0805_2012Metric,,fit
C6,100nF,Shields:C_0603_1608Metric,,fit
R6,2K2,Shields:R_0603_1608Metric,,fit
D1,GREEN LED,Shields:LED_0603_1608Metric,,fit
R5,470R,Shields:R_0603_1608Metric,,fit
J1,GND / +5V / OUT,Shields:JST_EH_B3B-EH-A_1x03_P2.50mm_Vertical,B3B-EH-A,fit
TP1,MICOUT,Shields:TestPin_1x01_P2.54mm,,fit
TP2,GND,Shields:TestPin_1x01_P2.54mm,,fit
JP1,GAIN SELECT / HEADER + SHUNT,Shields:Flex_Gain_Selector,Gold plated 1x03 2.54mm vertical header + removable 1x02 shunt,fit
JP2,AR SELECT / HEADER + SHUNT,Shields:Flex_AR_Selector,Gold plated 1x03 2.54mm vertical header + removable 1x02 shunt,fit
J2,LEFT / DOWNWARD MODULE,Shields:Flex_Socket_Left_Overhang,1x05 P2.54mm horizontal female socket; verify purchased dimensions,fit
J3,RIGHT / DOWNWARD MODULE,Shields:Flex_Socket_Right_Overhang,1x05 P2.54mm horizontal female socket; verify purchased dimensions,fit
